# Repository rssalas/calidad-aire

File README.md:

# flutter_application_1

IoT Air Quality - Universidad popular del cesar.

## Getting Started

SISTEMA DE MONITOREO Y ALERTAS TEMPRANAS PARA VARIABLES DE LA CALIDAD DEL AIRE BAJO UN ENTORNO IOT EN LA E.S.E HOSPITAL SANTACRUZ DE URUMITA LA GUAJIRA.

Garantizar la salud y el bienestar de las personas es un factor determinante, especialmente en entornos sensibles como lo son los hospitales, en estos espacios interiores, la presencia de contaminantes atmosféricos como el material particulado (PM2.5 y PM10), gases tóxicos como el monóxido de carbono (CO) y el dióxido de nitrógeno (NO₂), así mismo como condiciones inadecuadas de humedad y temperatura, inciden negativamente en la salud de pacientes y trabajadores del sector, por lo cual se hace necesario tener una buena calidad del aire en estos entornos. En el presente proyecto se propone el diseño y desarrollo de un sistema de monitoreo y alertas tempranas basado en un entorno IoT para ser implementado en la ESE Hospital Santa Cruz de Urumita, ubicado en el departamento de la Guajira. Gracias a los diferentes avances tecnológicos de la información y comunicación como lo es el internet de las cosas (IoT), se puede implementar este sistema inteligente donde se realiza un monitoreo ambiental, el cual permite supervisar en tiempo real variables ambientales, facilita la toma de decisiones mediante los riesgos sanitarios y genera una alerta tempranas, con este proyecto se busca dar respuesta a la necesidad de controlar la calidad del aire en el hospital y no solo garantizar el cumplimiento de los estándares de la calidad del aire establecidos la Organización Mundial de la Salud (OMS), si no también promover un entorno más seguro y saludable para todos los usuarios del hospital.

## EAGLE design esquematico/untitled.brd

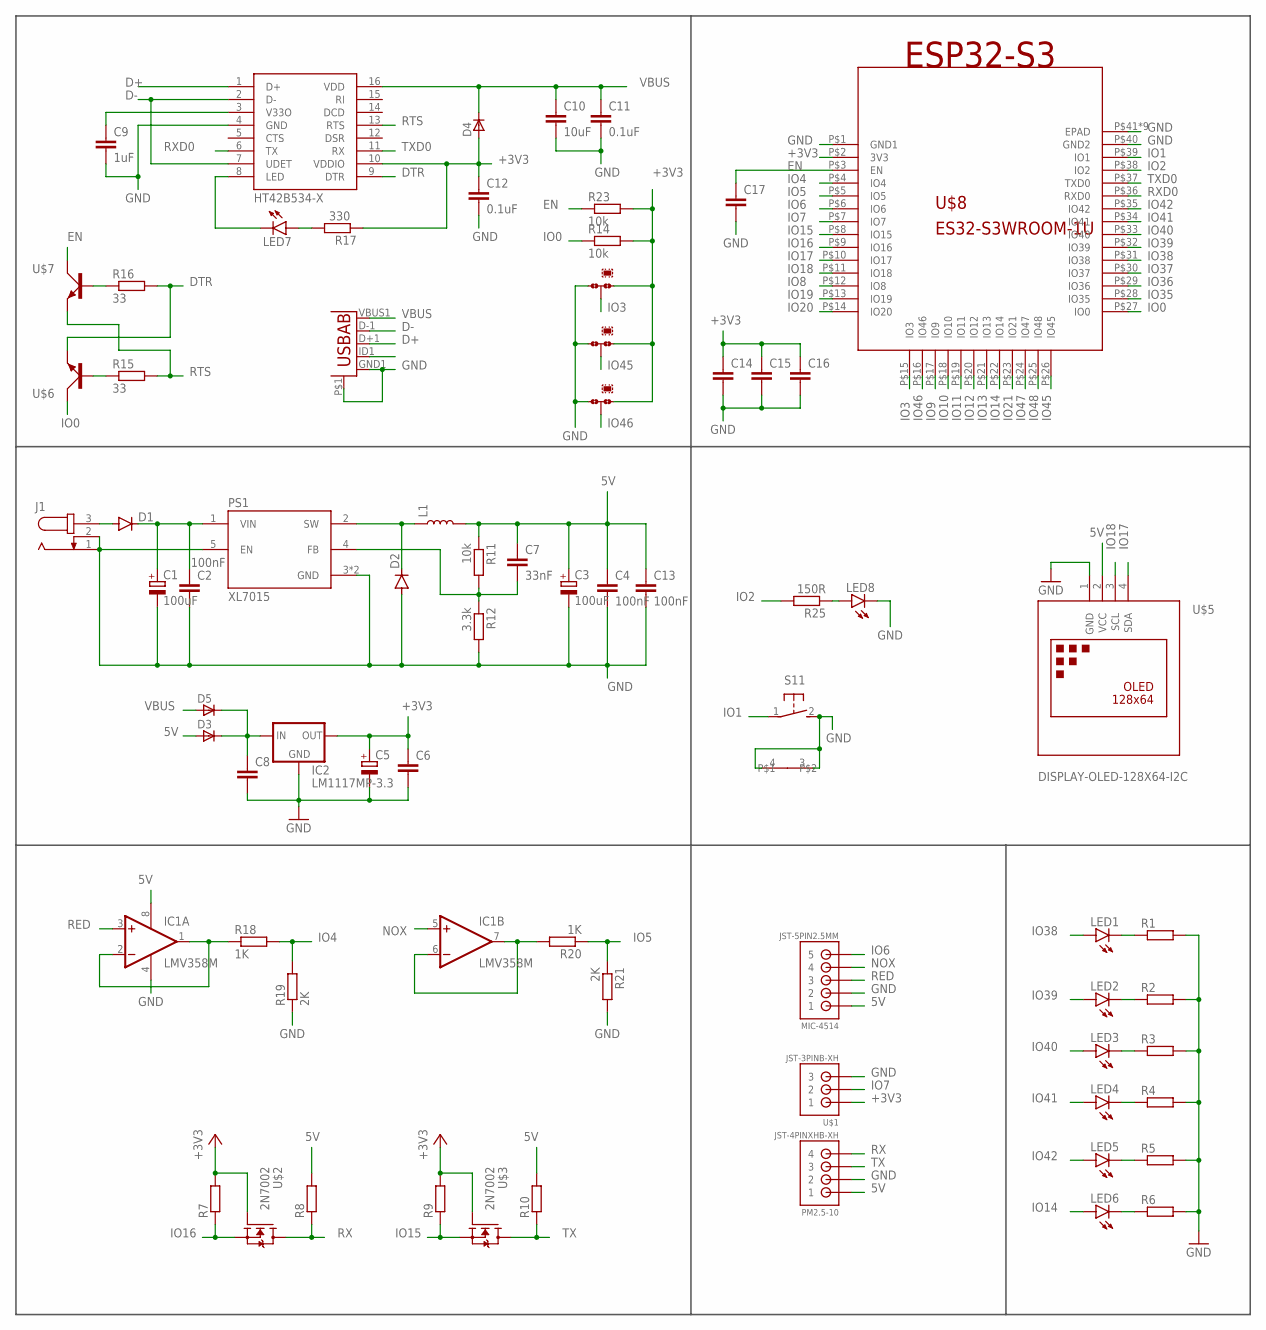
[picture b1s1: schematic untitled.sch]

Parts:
C1, C3: 100uF; E2,5-6
C2, C4, C13: 100nF; C0805K
C5: CPOL-EUE2.5-6; E2,5-6
C6, C8, C14, C15, C17: C-EUC0805K; C0805K
C7: 33nF; C0805K
C9: 1uF; C0805K
C10: 10uF; C0805K
C11, C12: 0.1uF; C0805K
C16: C-EUC1210K; C1210K
D1, D2: DIODE-DO214AA; DO214AA
D3, D4, D5: 1N4448WS; SOD323F
IC1: LMV358M; SO08
IC2: LM1117MP-3.3; SOT223
J1: JACK-PLUG0; SPC4077
JMP1, JMP2, JMP3: 0R-JUMPA; A0R-JMP
L1: 68µH/±20%/1.05A; CR75
LED1, LED2, LED3, LED4, LED5, LED6: LED3MM
LED7, LED8: LEDCHIPLED_0805; CHIPLED_0805
MIC-4514: JST-5PIN2.5MM; B5B-XH
PM2.5-10: JST-4PINXHB-XH; B4B-XH
PS1: XL7015; CONV_XL7015
R1, R2, R3, R4, R5, R6, R7, R8, R9, R10: R-EU_R0805W; R0805W
R11, R14, R23: 10k; R0805W
R12: 3.3k; R0805W
R15, R16: 33; R0805W
R17: 330; R0805W
R18, R20: 1K; R0805W
R19, R21: 2K; R0805W
R25: 150R; R0805W
S1: 31-XX; B3F-31XX
U2: USB""; USB-MICRO-SMD
U$1: JST-3PINB-XH; B3B-XH
U$2, U$3: 2N7002; SOT23
U$4: HT42B534-X; SOP16
U$5: DISPLAY-OLED-128X64-I2C
U$6, U$7: MMBT4401; SOT23
U$8: ES32-S3WROOM-1U; ESP32-S3-WROOM-1U

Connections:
5V: C3.+, C4.1, C7.1, C13.1, D3.A, IC1.8 (V+), L1.P$2 (2), MIC-4514.P$1 (1), PM2.5-10.P$1 (1), R8.2, R10.2, R11.1, U$5.2 (VCC)
+3V3: C5.+, C6.1, C12.1, C14.1, C15.1, C16.1, D4.A, IC2.2 (OUT), IC2.4 (OUT), JMP1.1, JMP2.1, JMP3.1, R7.2, R9.2, R14.2, R17.1, R23.2, U$1.P$1 (1), U$2.1 (G), U$3.1 (G), U$4.10 (VDDIO), U$8.P$2 (3V3)
D+: U2.D+1 (D+), U$4.1 (D+)
D-: U2.D-1 (D-), U$4.2 (D-), U$4.7 (UDET)
DTR: R16.2, U$4.9 (DTR), U$6.2 (E)
EN: C17.1, R23.1, U$7.3 (C), U$8.P$3 (EN)
GND: C1.-, C2.2, C3.-, C4.2, C5.-, C6.2, C8.2, C9.2, C10.2, C11.2, C12.2, C13.2, C14.2, C15.2, C16.2, C17.2, D2.A, IC1.4 (V-), IC2.1 (GND), J1.1, J1.2, JMP1.3, JMP2.3, JMP3.3, LED8.C, MIC-4514.P$2 (2), PM2.5-10.P$2 (2), PS1.3 (GND), PS1.5 (EN), PS1.6 (GND), R1.2, R2.2, R3.2, R4.1, R5.1, R6.1, R12.2, R19.1, R21.2, S1.2 (S), S1.3, S1.4, U2.GND1 (GND), U2.P$1 (GND1), U$1.P$3 (3), U$4.4 (GND), U$5.1 (GND), U$8.P$1 (GND1), U$8.P$40 (GND2), U$8.P$41 (EPAD), U$8.P$42 (EPAD), U$8.P$43 (EPAD), U$8.P$44 (EPAD), U$8.P$45 (EPAD), U$8.P$46 (EPAD), U$8.P$47 (EPAD), U$8.P$48 (EPAD), U$8.P$49 (EPAD)
IO0: R14.1, U$6.3 (C), U$8.P$27 (IO0)
IO1: S1.1, U$8.P$39 (IO1)
IO2: R25.2, U$8.P$38 (IO2)
IO3: JMP1.2, U$8.P$15 (IO3)
IO4: R18.2, R19.2, U$8.P$4 (IO4)
IO5: R20.1, R21.1, U$8.P$5 (IO5)
IO6: MIC-4514.P$5 (5), U$8.P$6 (IO6)
IO7: U$1.P$2 (2), U$8.P$7 (IO7)
IO8: U$8.P$12 (IO8)
IO9: U$8.P$17 (IO9)
IO10: U$8.P$18 (IO10)
IO11: U$8.P$19 (IO11)
IO12: U$8.P$20 (IO12)
IO13: U$8.P$21 (IO13)
IO14: LED6.A, U$8.P$22 (IO14)
IO15: R9.1, U$3.2 (S), U$8.P$8 (IO15)
IO16: R7.1, U$2.2 (S), U$8.P$9 (IO16)
IO17: U$5.4 (SDA), U$8.P$10 (IO17)
IO18: U$5.3 (SCL), U$8.P$11 (IO18)
IO19: U$8.P$13 (IO19)
IO20: U$8.P$14 (IO20)
IO21: U$8.P$23 (IO21)
IO35: U$8.P$28 (IO35)
IO36: U$8.P$29 (IO36)
IO37: U$8.P$30 (IO37)
IO38: LED1.A, U$8.P$31 (IO38)
IO39: LED2.A, U$8.P$32 (IO39)
IO40: LED3.A, U$8.P$33 (IO40)
IO41: LED4.A, U$8.P$34 (IO41)
IO42: LED5.A, U$8.P$35 (IO42)
IO45: JMP2.2, U$8.P$26 (IO45)
IO46: JMP3.2, U$8.P$16 (IO46)
IO47: U$8.P$24 (IO47)
IO48: U$8.P$25 (IO48)
unnamed: D1.A, J1.3
unnamed: C1.+, C2.1, D1.C, PS1.1 (VIN)
unnamed: C8.1, D3.C, D5.C, IC2.3 (IN)
unnamed: D2.C, L1.P$1 (1), PS1.2 (SW)
unnamed: LED1.K (C), R1.1
unnamed: C7.2, PS1.4 (FB), R11.2, R12.1
unnamed: R15.1, U$6.1 (B)
unnamed: IC1.1 (OUT), IC1.2 (-IN), R18.1
unnamed: IC1.6 (-IN), IC1.7 (OUT), R20.2
unnamed: C9.1, U$4.3 (V33O)
unnamed: LED8.A, R25.1
unnamed: LED2.K (C), R2.1
unnamed: R16.1, U$7.1 (B)
unnamed: LED7.C, U$4.8 (LED)
unnamed: LED3.K (C), R3.1
unnamed: LED7.A, R17.2
unnamed: LED4.K (C), R4.2
unnamed: LED5.K (C), R5.2
unnamed: LED6.K (C), R6.2
NOX: IC1.5 (+IN), MIC-4514.P$4 (4)
RED: IC1.3 (+IN), MIC-4514.P$3 (3)
RTS: R15.2, U$4.13 (RTS), U$7.2 (E)
RX: PM2.5-10.P$4 (4), R8.1, U$2.3 (D)
RXD0: U$4.6 (TX), U$8.P$36 (RXD0)
TX: PM2.5-10.P$3 (3), R10.1, U$3.3 (D)
TXD0: U$4.11 (RX), U$8.P$37 (TXD0)
VBUS: C10.1, C11.1, D4.C, D5.A, U2.VBUS1 (VBUS), U$4.16 (VDD)

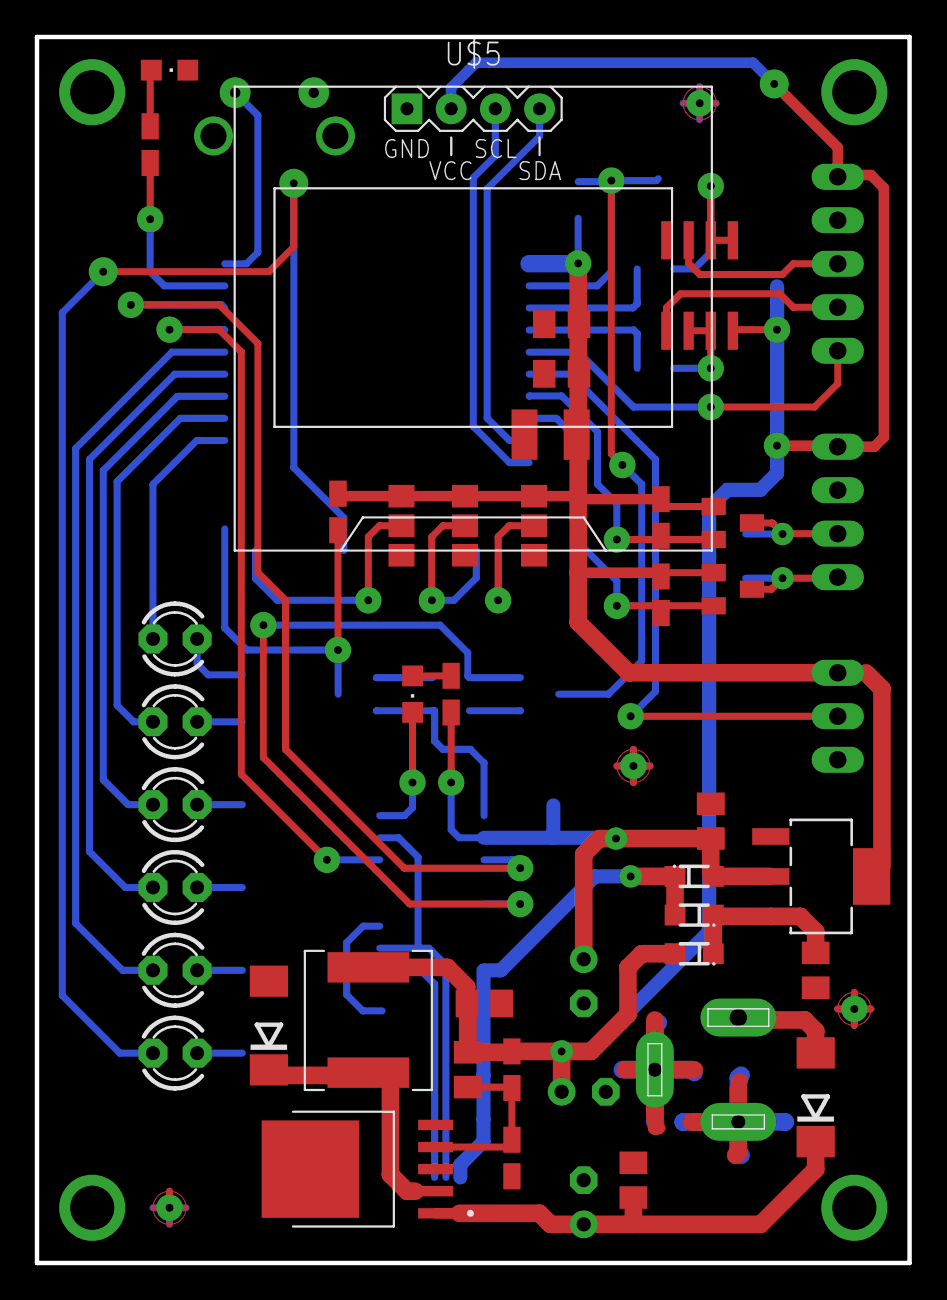
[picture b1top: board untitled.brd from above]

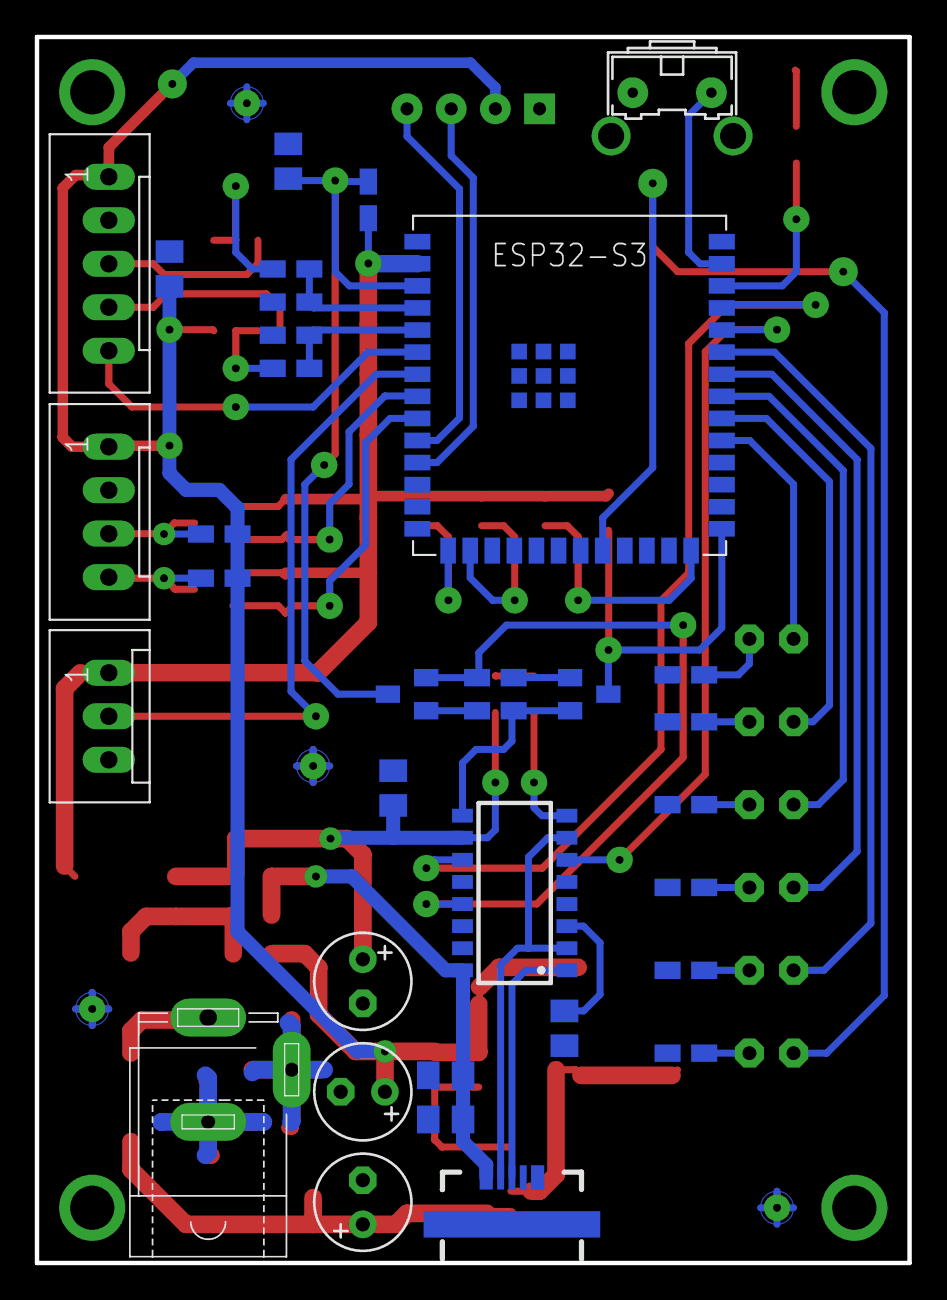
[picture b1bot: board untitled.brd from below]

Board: 2 copper layers, 50.2 x 70.5 mm, 72 parts (34 on the bottom side), 54 nets.

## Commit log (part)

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2026-02-05 primer commit randolf

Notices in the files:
parts and their libraries:
SparkFun-Coils: Licensing: Creative Commons ShareAlike 4.0 International - https://creativecommons.org/licenses/by-sa/4.0
diy-modules: Released under the Creative Commons Attribution 4.0 International License: http://creativecommons.org/licenses/by/4.0
